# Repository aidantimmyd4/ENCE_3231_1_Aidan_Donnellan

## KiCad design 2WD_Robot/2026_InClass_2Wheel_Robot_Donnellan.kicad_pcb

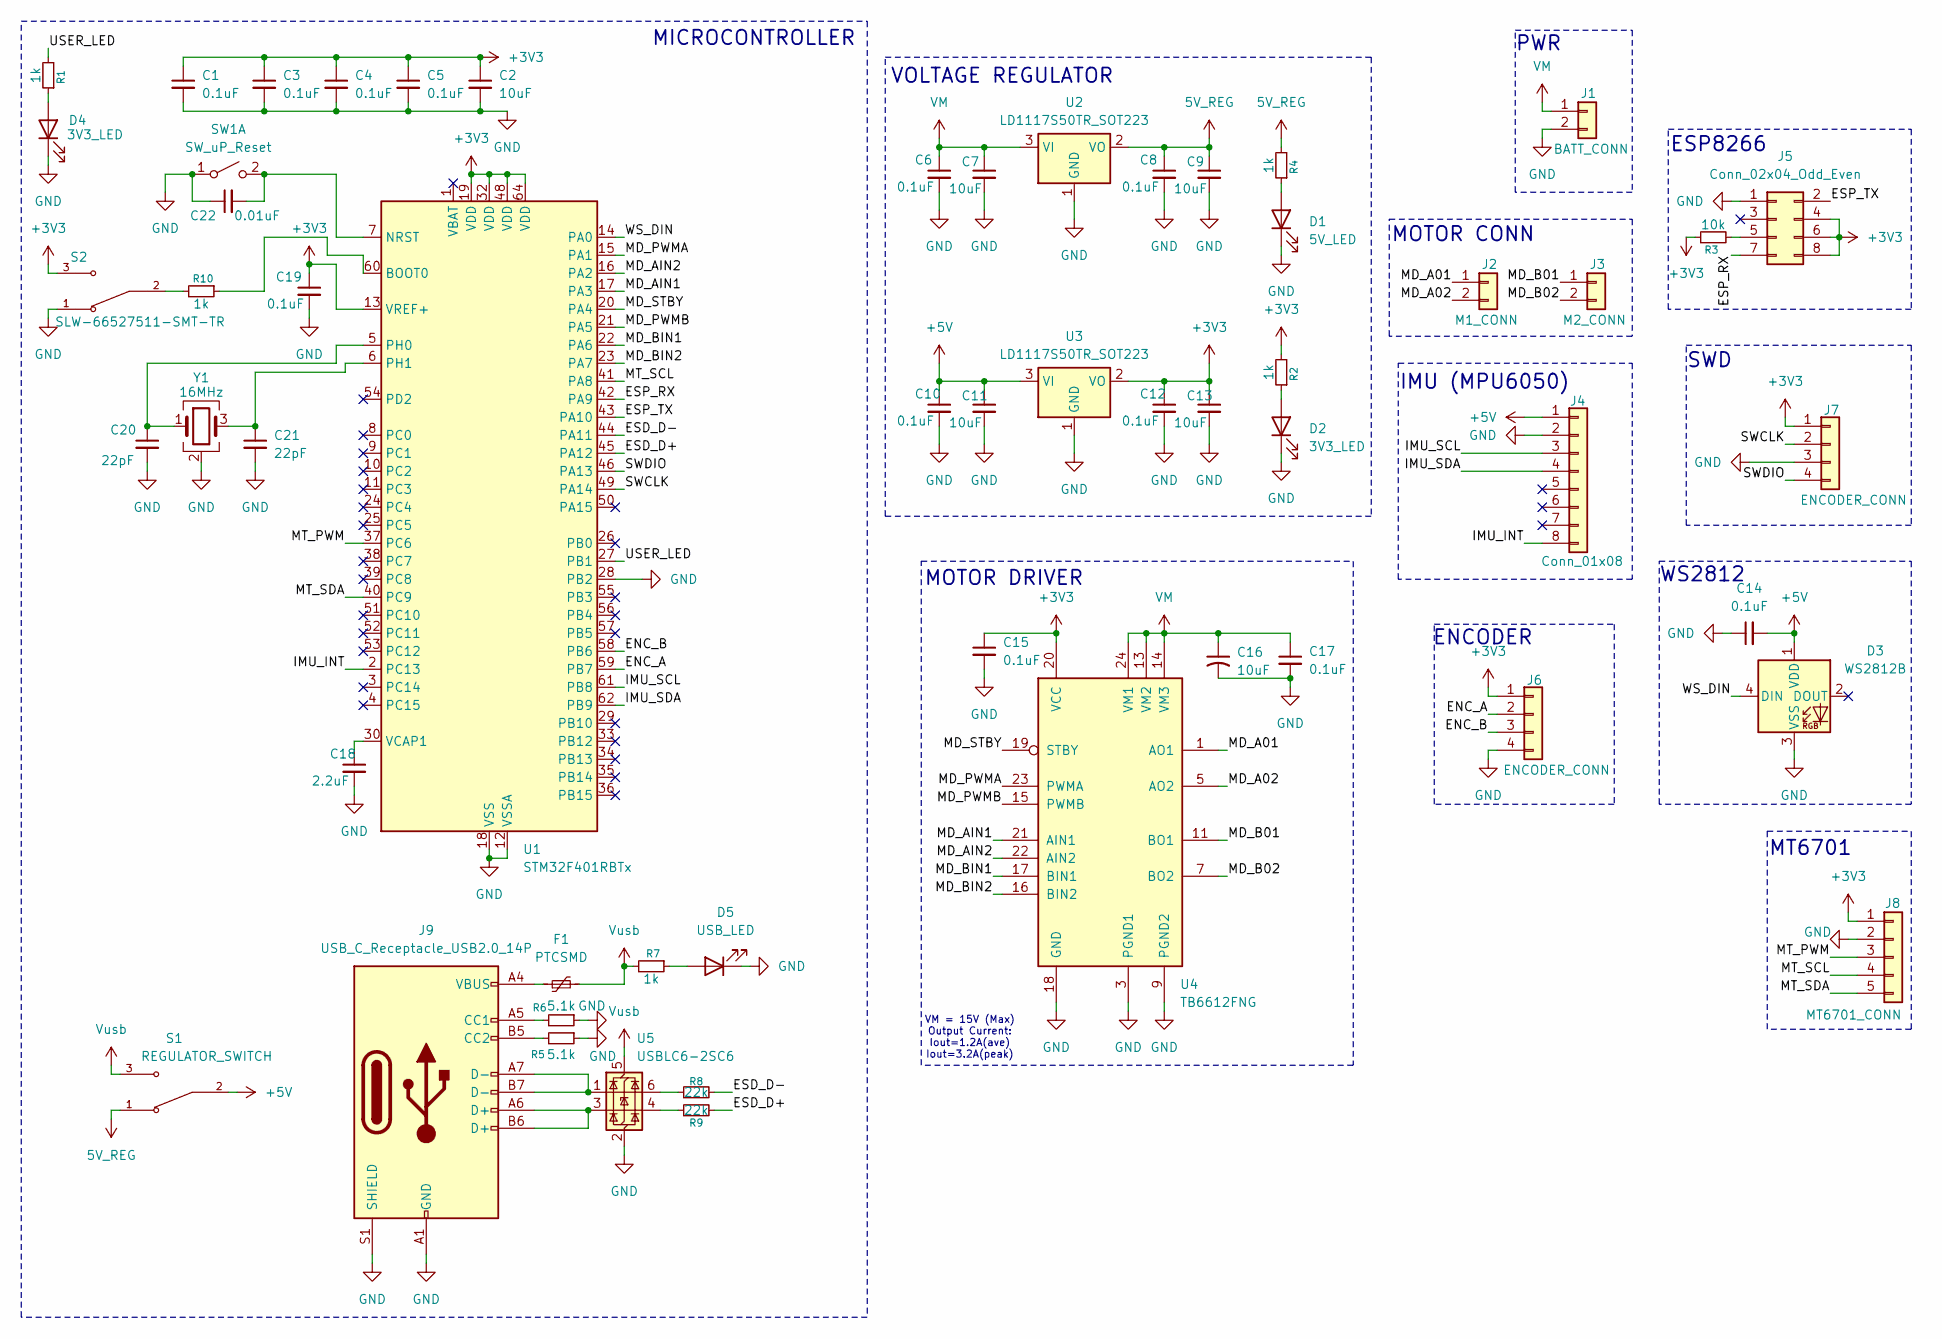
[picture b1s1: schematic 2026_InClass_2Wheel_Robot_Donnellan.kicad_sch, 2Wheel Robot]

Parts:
C1, C3, C4, C5, C6, C8, C10, C12, C14, C15, C17, C19: 0.1uF; C_0805_2012Metric_Pad1.18x1.45mm_HandSolder; Mfr # KAM21BR71H104JM; Mouser # 581-KAM21BR71H104JM
C2, C7, C9, C11, C13: 10uF; C_0805_2012Metric_Pad1.18x1.45mm_HandSolder; Mfr # 0805X7R106KT1AT; Mouser # 581-0805X7R106KT1AT
C16: 10uF; C_0805_2012Metric_Pad1.18x1.45mm_HandSolder
C18: 2.2uF; C_0805_2012Metric_Pad1.18x1.45mm_HandSolder; Mfr # KAM21BR71H104JM; Mouser # 581-KAM21BR71H104JM
C20, C21: 22pF; C_0805_2012Metric_Pad1.18x1.45mm_HandSolder; Mfr # KAM21BR71H104JM; Mouser # 581-KAM21BR71H104JM
C22: 0.01uF; C_0805_2012Metric_Pad1.18x1.45mm_HandSolder; Mfr # KAM21BR71H104JM; Mouser # 581-KAM21BR71H104JM
D1: 5V_LED; LED_0805_2012Metric_Pad1.15x1.40mm_HandSolder
D2, D4: 3V3_LED; LED_0805_2012Metric_Pad1.15x1.40mm_HandSolder
D3: WS2812B; LED_WS2812B_PLCC4_5.0x5.0mm_P3.2mm
D5: USB_LED; LED_0805_2012Metric_Pad1.15x1.40mm_HandSolder
F1: PTCSMD; Fuse_1812_4532Metric
J1: BATT_CONN; JST_XH_B2B-XH-A_1x02_P2.50mm_Vertical
J2: M1_CONN; JST_XH_B2B-XH-A_1x02_P2.50mm_Vertical
J3: M2_CONN; JST_XH_B2B-XH-A_1x02_P2.50mm_Vertical
J4: Conn_01x08; PinSocket_1x08_P2.54mm_Vertical
J5: Conn_02x04_Odd_Even; PinSocket_2x04_P2.54mm_Vertical
J6: ENCODER_CONN; JST_XH_B4B-XH-A_1x04_P2.50mm_Vertical
J7: ENCODER_CONN; PinHeader_1x04_P2.54mm_Vertical
J8: MT6701_CONN; JST_XH_B5B-XH-A_1x05_P2.50mm_Vertical
J9: USB_C_Receptacle_USB2.0_14P; USB_C_Receptacle_HCTL_HC-TYPE-C-16P-01A
R1, R2, R4, R7, R10: 1k; R_0805_2012Metric_Pad1.20x1.40mm_HandSolder; Mfr # RV0805JR-0710KL
R3: 10k; R_0805_2012Metric_Pad1.20x1.40mm_HandSolder; Mfr # RV0805JR-0710KL
R5, R6: 5.1k; R_0805_2012Metric_Pad1.20x1.40mm_HandSolder
R8, R9: 22k; R_0805_2012Metric_Pad1.20x1.40mm_HandSolder
S1: REGULATOR_SWITCH; SW_SLW-66527511-SMT-TR; PARTREV 1.01
S2: SLW-66527511-SMT-TR; SW_SLW-66527511-SMT-TR; PARTREV 1.01
SW1: SW_uP_Reset
U1: STM32F401RBTx; LQFP-64_10x10mm_P0.5mm; Manufacutre # STM32F401RET6; Mouser # 511-STM32F401RET6
U2, U3: LD1117S50TR_SOT223; SOT-223-3_TabPin2; Mfr # LD1117S50TR
U4: TB6612FNG; SSOP-24_5.3x8.2mm_P0.65mm
U5: USBLC6-2SC6; SOT-23-6
Y1: 16MHz; Crystal_SMD_Abracon_ABM8G-4Pin_3.2x2.5mm

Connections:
5V_REG: C8.1, C9.1, R4.2, S1.1, U2.2 (VO)
+3V3: C1.1, C2.1, C3.1, C4.1, C5.1, C12.1, C13.1, C15.1, C19.1, J5.4, J5.6, J5.8, J6.1, J7.1, J8.1, R2.2, R3.1, S2.3, U1.13 (VREF+), U1.19 (VDD), U1.32 (VDD), U1.48 (VDD), U1.64 (VDD), U3.2 (VO), U4.20 (VCC)
+5V: C10.1, C11.1, C14.2, D3.1 (VDD), J4.1, S1.2, U3.3 (VI)
/ENC_A: J6.2, U1.59 (PB7)
/ENC_B: J6.3, U1.58 (PB6)
/ESD_D+: R9.2, U1.45 (PA12)
/ESD_D-: R8.2, U1.44 (PA11)
/ESP_RX: J5.7, U1.42 (PA9)
/ESP_TX: J5.2, U1.43 (PA10)
/IMU_INT: J4.8, U1.2 (PC13)
/IMU_SCL: J4.3, U1.61 (PB8)
/IMU_SDA: J4.4, U1.62 (PB9)
/MD_A01: J2.1, U4.1 (AO1), U4.2 (AO1)
/MD_A02: J2.2, U4.5 (AO2), U4.6 (AO2)
/MD_AIN1: U1.17 (PA3), U4.21 (AIN1)
/MD_AIN2: U1.16 (PA2), U4.22 (AIN2)
/MD_B01: J3.1, U4.11 (BO1), U4.12 (BO1)
/MD_B02: J3.2, U4.7 (BO2), U4.8 (BO2)
/MD_BIN1: U1.22 (PA6), U4.17 (BIN1)
/MD_BIN2: U1.23 (PA7), U4.16 (BIN2)
/MD_PWMA: U1.15 (PA1), U4.23 (PWMA)
/MD_PWMB: U1.21 (PA5), U4.15 (PWMB)
/MD_STBY: U1.20 (PA4), U4.19 (STBY)
/MT_PWM: J8.3, U1.37 (PC6)
/MT_SCL: J8.4, U1.41 (PA8)
/MT_SDA: J8.5, U1.40 (PC9)
/SWCLK: J7.2, U1.49 (PA14)
/SWDIO: J7.4, U1.46 (PA13)
/USER_LED: R1.2, U1.27 (PB1)
/WS_DIN: D3.4 (DIN), U1.14 (PA0)
GND: C1.2, C2.2, C3.2, C4.2, C5.2, C6.2, C7.2, C8.2, C9.2, C10.2, C11.2, C12.2, C13.2, C14.1, C15.2, C16.2, C17.2, C18.2, C19.2, C20.2, C21.2, C22.1, D1.1 (K), D2.1 (K), D3.3 (VSS), D4.1 (K), D5.1 (K), J1.2, J4.2, J5.1, J6.4, J7.3, J8.2, J9.A1 (GND), J9.A12 (GND), J9.B1 (GND), J9.B12 (GND), J9.S1 (SHIELD), R5.1, R6.1, S2.1, SW1.1 (A), U1.12 (VSSA), U1.18 (VSS), U1.28 (PB2), U1.31 (VSS), U1.47 (VSS), U1.63 (VSS), U2.1 (GND), U3.1 (GND), U4.3 (PGND1), U4.4 (PGND1), U4.9 (PGND2), U4.10 (PGND2), U4.18 (GND), U5.2 (GND), Y1.2 (G), Y1.4 (G)
unnamed: D1.2 (A), R4.1
unnamed: D2.2 (A), R2.1
unnamed: D4.2 (A), R1.1
unnamed: D5.2 (A), R7.1
unnamed: F1.1, J9.A4 (VBUS), J9.A9 (VBUS), J9.B4 (VBUS), J9.B9 (VBUS)
unnamed: J5.5, R3.2
unnamed: J9.A5 (CC1), R6.2
unnamed: J9.B5 (CC2), R5.2
unnamed: J9.A6 (D+), J9.B6 (D+), U5.3 (I/O2)
unnamed: J9.A7 (D-), J9.B7 (D-), U5.1 (I/O1)
unnamed: R8.1, U5.6 (I/O1)
unnamed: R9.1, U5.4 (I/O2)
unnamed: R10.2, S2.2
unnamed: C22.2, SW1.2 (B), U1.7 (NRST)
unnamed: R10.1, U1.60 (BOOT0)
unnamed: C20.1, U1.5 (PH0), Y1.1
unnamed: C21.1, U1.6 (PH1), Y1.3
unnamed: C18.1, U1.30 (VCAP1)
VM: C6.1, C7.1, C16.1, C17.1, J1.1, U2.3 (VI), U4.13 (VM2), U4.14 (VM3), U4.24 (VM1)
Vusb: F1.2, R7.2, S1.3, U5.5 (VBUS)

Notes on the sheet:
WS2812
ESP8266
MICROCONTROLLER
ENCODER
PWR
MT6701
MOTOR CONN
SWD
VOLTAGE REGULATOR
VM = 15V (Max) Output Current: Iout=1.2A(ave) Iout=3.2A(peak)
IMU (MPU6050)
MOTOR DRIVER

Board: 2 copper layers, 56 parts (0 on the bottom side), 51 nets, no tracks yet.

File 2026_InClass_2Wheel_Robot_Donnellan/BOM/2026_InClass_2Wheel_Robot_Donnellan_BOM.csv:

"Reference","Qty","Value","DNP","Exclude from BOM","Exclude from Board","Footprint","Datasheet"
"C1,C3,C4,C5,C6,C8,C10,C12,C14,C15,C17,C19","12","0.1uF","","","","Capacitor_SMD:C_0805_2012Metric_Pad1.18x1.45mm_HandSolder",""
"C2,C7,C9,C11,C13","5","10uF","","","","Capacitor_SMD:C_0805_2012Metric_Pad1.18x1.45mm_HandSolder",""
"C16","1","10uF","","","","Capacitor_Tantalum_SMD:CP_EIA-6032-28_Kemet-C_HandSolder",""
"C18","1","2.2uF","","","","Capacitor_SMD:C_0805_2012Metric_Pad1.18x1.45mm_HandSolder",""
"C20,C21","2","22pF","","","","Capacitor_SMD:C_0805_2012Metric_Pad1.18x1.45mm_HandSolder",""
"C22","1","0.01uF","","","","Capacitor_SMD:C_0805_2012Metric_Pad1.18x1.45mm_HandSolder",""
"D1","1","5V_LED","","","","LED_SMD:LED_0805_2012Metric_Pad1.15x1.40mm_HandSolder",""
"D2,D4","2","3V3_LED","","","","LED_SMD:LED_0805_2012Metric_Pad1.15x1.40mm_HandSolder",""
"D3","1","WS2812B","","","","LED_SMD:LED_WS2812B_PLCC4_5.0x5.0mm_P3.2mm","https://cdn-shop.adafruit.com/datasheets/WS2812B.pdf"
"D5","1","USB_LED","","","","LED_SMD:LED_0805_2012Metric_Pad1.15x1.40mm_HandSolder",""
"F1","1","PTCSMD","","","","Fuse:Fuse_1812_4532Metric",""
"J1","1","BATT_CONN","","","","Connector_JST:JST_XH_B2B-XH-A_1x02_P2.50mm_Vertical",""
"J2","1","M1_CONN","","","","Connector_JST:JST_XH_B2B-XH-A_1x02_P2.50mm_Vertical",""
"J3","1","M2_CONN","","","","Connector_JST:JST_XH_B2B-XH-A_1x02_P2.50mm_Vertical",""
"J4","1","Conn_01x08","","","","Connector_PinSocket_2.54mm:PinSocket_1x08_P2.54mm_Vertical",""
"J5","1","Conn_02x04_Odd_Even","","","","Connector_PinSocket_2.54mm:PinSocket_2x04_P2.54mm_Vertical",""
"J6","1","ENCODER_CONN","","","","Connector_JST:JST_XH_B4B-XH-A_1x04_P2.50mm_Vertical",""
"J7","1","ENCODER_CONN","","","","Connector_PinHeader_2.54mm:PinHeader_1x04_P2.54mm_Vertical",""
"J8","1","MT6701_CONN","","","","Connector_JST:JST_XH_B5B-XH-A_1x05_P2.50mm_Vertical",""
"J9","1","USB_C_Receptacle_USB2.0_14P","","","","Connector_USB:USB_C_Receptacle_HCTL_HC-TYPE-C-16P-01A","https://www.usb.org/sites/default/files/documents/usb_type-c.zip"
"R1,R2,R4,R7,R10","5","1k","","","","Resistor_SMD:R_0805_2012Metric_Pad1.20x1.40mm_HandSolder",""
"R3","1","10k","","","","Resistor_SMD:R_0805_2012Metric_Pad1.20x1.40mm_HandSolder",""
"R5,R6","2","5.1k","","","","Resistor_SMD:R_0805_2012Metric_Pad1.20x1.40mm_HandSolder",""
"R8,R9","2","22k","","","","Resistor_SMD:R_0805_2012Metric_Pad1.20x1.40mm_HandSolder",""
"S1","1","REGULATOR_SWITCH","","","","SW_SLW-66527511-SMT-TR:SW_SLW-66527511-SMT-TR",""
"S2","1","SLW-66527511-SMT-TR","","","","SW_SLW-66527511-SMT-TR:SW_SLW-66527511-SMT-TR",""
"SW1","1","SW_uP_Reset","","","","SW_uP_Reset:SW_uP_Reset",""
"U1","1","STM32F401RBTx","","","","Package_QFP:LQFP-64_10x10mm_P0.5mm","https://www.st.com/resource/en/datasheet/stm32f401rb.pdf"
"U2,U3","2","LD1117S50TR_SOT223","","","","Package_TO_SOT_SMD:SOT-223-3_TabPin2","http://www.st.com/st-web-ui/static/active/en/resource/techni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"
"U4","1","TB6612FNG","","","","Package_SO:SSOP-24_5.3x8.2mm_P0.65mm","https://toshiba.semicon-storage.com/us/product/linear/motord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"
"U5","1","USBLC6-2SC6","","","","Package_TO_SOT_SMD:SOT-23-6","https://www.st.com/resource/en/datasheet/usblc6-2.pdf"
"Y1","1","16MHz","","","","Crystal:Crystal_SMD_Abracon_ABM8G-4Pin_3.2x2.5mm",""

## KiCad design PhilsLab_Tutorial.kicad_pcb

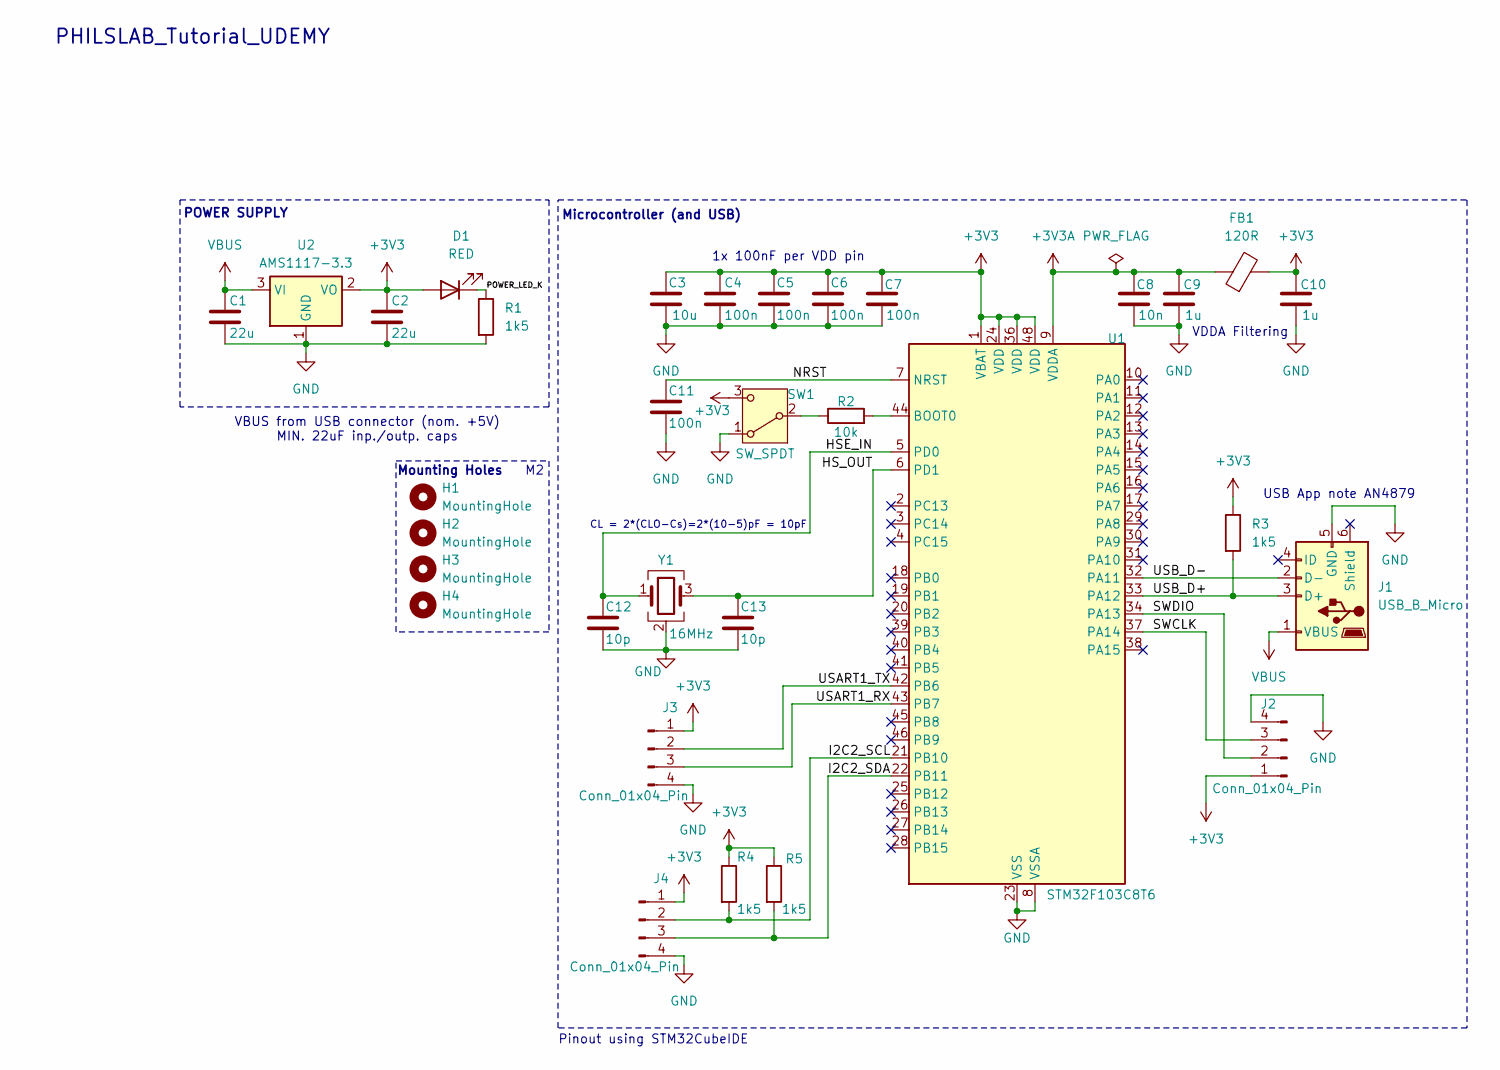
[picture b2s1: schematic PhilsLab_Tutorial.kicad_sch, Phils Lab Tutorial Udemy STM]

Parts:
C1, C2: 22u; C_0805_2012Metric
C3: 10u; C_0603_1608Metric
C4, C5, C6, C7, C11: 100n; C_0402_1005Metric
C8: 10n; C_0402_1005Metric
C9, C10: 1u; C_0402_1005Metric
C12, C13: 10p; C_0402_1005Metric
D1: RED; LED_0603_1608Metric
FB1: 120R; L_0603_1608Metric
H1, H2, H3, H4: MountingHole; MountingHole_2.2mm_M2
J1: USB_B_Micro; USB_Micro-B_Wuerth_629105150521
J2, J3, J4: Conn_01x04_Pin; PinHeader_1x04_P2.54mm_Vertical
R1, R3, R4, R5: 1k5; R_0402_1005Metric
R2: 10k; R_0402_1005Metric
SW1: SW_SPDT; SW_SPDT_PCM12
U1: STM32F103C8T6; LQFP-48_7x7mm_P0.5mm
U2: AMS1117-3.3; SOT-223-3_TabPin2
Y1: 16MHz; Crystal_SMD_3225-4Pin_3.2x2.5mm

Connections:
+3V3: C2.1, C3.1, C4.1, C5.1, C6.1, C7.1, C10.1, D1.2 (A), FB1.2, J2.1, J3.1, J4.1, R3.1, R4.1, R5.1, SW1.3 (C), U1.1 (VBAT), U1.24 (VDD), U1.36 (VDD), U1.48 (VDD), U2.2 (VO)
+3V3A: C8.1, C9.1, FB1.1, U1.9 (VDDA)
/HSE_IN: C12.1, U1.5 (PD0), Y1.1
/HS_OUT: C13.1, U1.6 (PD1), Y1.3
/I2C2_SCL: J4.2, R4.2, U1.21 (PB10)
/I2C2_SDA: J4.3, R5.2, U1.22 (PB11)
/NRST: C11.1, U1.7 (NRST)
/POWER_LED_K: D1.1 (K), R1.1
/SWCLK: J2.3, U1.37 (PA14)
/SWDIO: J2.2, U1.34 (PA13)
/USART1_RX: J3.3, U1.43 (PB7)
/USART1_TX: J3.2, U1.42 (PB6)
/USB_D+: J1.3 (D+), R3.2, U1.33 (PA12); also elsewhere on the board
/USB_D-: J1.2 (D-), U1.32 (PA11); also elsewhere on the board
GND: C1.2, C2.2, C3.2, C4.2, C5.2, C6.2, C7.2, C8.2, C9.2, C10.2, C11.2, C12.2, C13.2, J1.5 (GND), J2.4, J3.4, J4.4, R1.2, SW1.1 (A), U1.8 (VSSA), U1.23 (VSS), U1.35 (VSS), U1.47 (VSS), U2.1 (GND), Y1.2 (G), Y1.4 (G); also elsewhere on the board
unnamed: R2.1, SW1.2 (B)
unnamed: R2.2, U1.44 (BOOT0)
VBUS: C1.1, J1.1 (VBUS), U2.3 (VI); also elsewhere on the board

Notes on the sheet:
USB App note AN4879
Pinout using STM32CubeIDE
VBUS from USB connector (nom. +5V) MIN. 22uF inp./outp. caps
Mounting Holes
POWER SUPPLY
Microcontroller (and USB)
VDDA Filtering
CL = 2*(CLO-Cs)=2*(10-5)pF = 10pF
PHILSLAB_Tutorial_UDEMY
1x 100nF per VDD pin

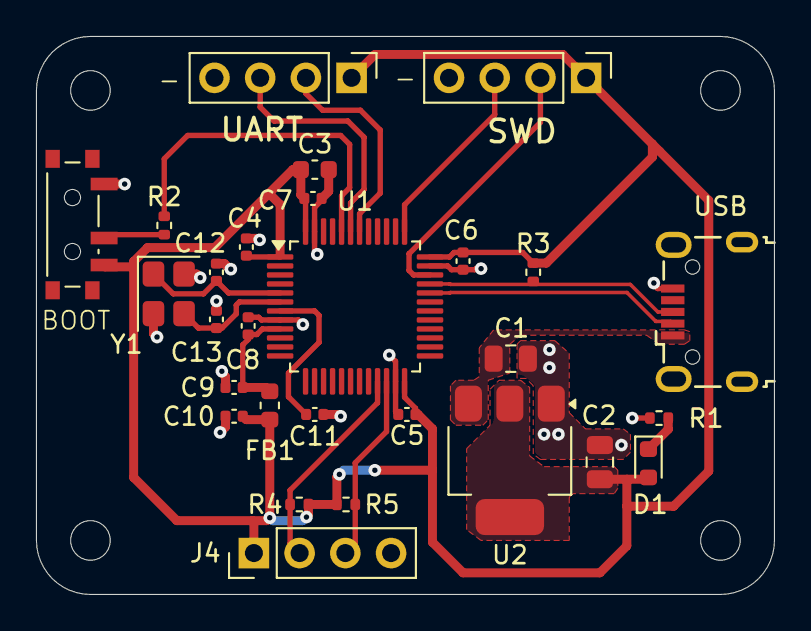
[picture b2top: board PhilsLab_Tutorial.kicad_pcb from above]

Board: 2 copper layers, 41.0 x 31.0 mm, 32 parts (0 on the bottom side), 18 nets.

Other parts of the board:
USB: USB_B_Micro; USB_Micro-B_Wuerth_629105150521

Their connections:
/USB_D+: USB.3 (D+); also elsewhere on the board
/USB_D-: USB.2 (D-); also elsewhere on the board
GND: USB.5 (GND); also elsewhere on the board
VBUS: USB.1 (VBUS); also elsewhere on the board

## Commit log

2026-04-16 Add README for Lab 1 of Embedded Systems Programming
2026-04-16 Rename Week3_InClass_HCSR04_interface.zip to Lab_1/Week3_InClass_HCSR04_interface.zip
2026-04-16 Rename Embedded_Lab1_BlockDiagram.pdf to Lab_1/Embedded_Lab1_BlockDiagram.pdf
2026-04-16 Rename Echo_Far.png to Lab_1/Echo_Far.png
2026-04-16 Rename Echo_Close.png to Lab_1/Echo_Close.png
2026-04-16 Rename 10us_Trigger.png to Lab_1/10us_Trigger.png
2026-04-23 Add README.md for project documentation
2026-04-23 Rename 2WD_Robot/print.pdf to 2WD_Robot/docs/print.pdf
2026-04-23 Add README.md for project components
2026-04-23 Add README.md for ESP8266 components
2026-04-23 Rename 2WD_Robot/components/ESP8266-01_ESP-01.kicad_mod to 2WD_Robot/components/ESP8266-01_ESP-01/ESP8266-01_ESP-01.kicad_mod
2026-04-23 Rename 2WD_Robot/components/ESP8266-01_ESP-01.kicad_sym to 2WD_Robot/components/ESP8266-01_ESP-01/ESP8266-01_ESP-01.kicad_sym
2026-04-23 Rename 2WD_Robot/components/ESP8266-01_ESP-01.step to 2WD_Robot/components/ESP8266-01_ESP-01/ESP8266-01_ESP-01.step
2026-04-23 Add README for Fuse 3D Model
2026-04-23 Add README for Reset Switch component
2026-04-27 Initial Commit of PhilsLab STM32 Video Tutorial
2026-04-27 Moved tutorial files into a dedicated subfolder
2026-05-03 Organizing ENCE 3231 repo with proper subfolders
2026-05-03 Re-organized ENCE 3231 repo
2026-05-03 Removing duplicates
2026-05-03 G. Martins version added
2026-05-03 Removed unnecessary files
2026-05-05 Revised PCB design
2026-05-05 Added BOM
2026-06-09 Phase D Documentation Added
2026-06-09 Fixed Phase D Documentation
2026-06-09 Untrack Phase D PDF reports from repository history
2026-06-09 Configure gitattributes to fix GitHub code rendering conflicts
2026-06-09 Add final Phase D PDF report
